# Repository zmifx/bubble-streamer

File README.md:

# How to fix S*daStream?
Somehow it happened that this bubbler stopped working-only the LEDs were flashing (no, a new power adapter did not help).
Attempts to repair the original control board did not work, it is simply too complicated for me. So I simply made a new PCB, radically simplified, built on an Arduino Micro and many of the original parts. Here are some data files. NO WARRANTY, FOR STUDY PURPOSES ONLY!
* The original one

* New PCB

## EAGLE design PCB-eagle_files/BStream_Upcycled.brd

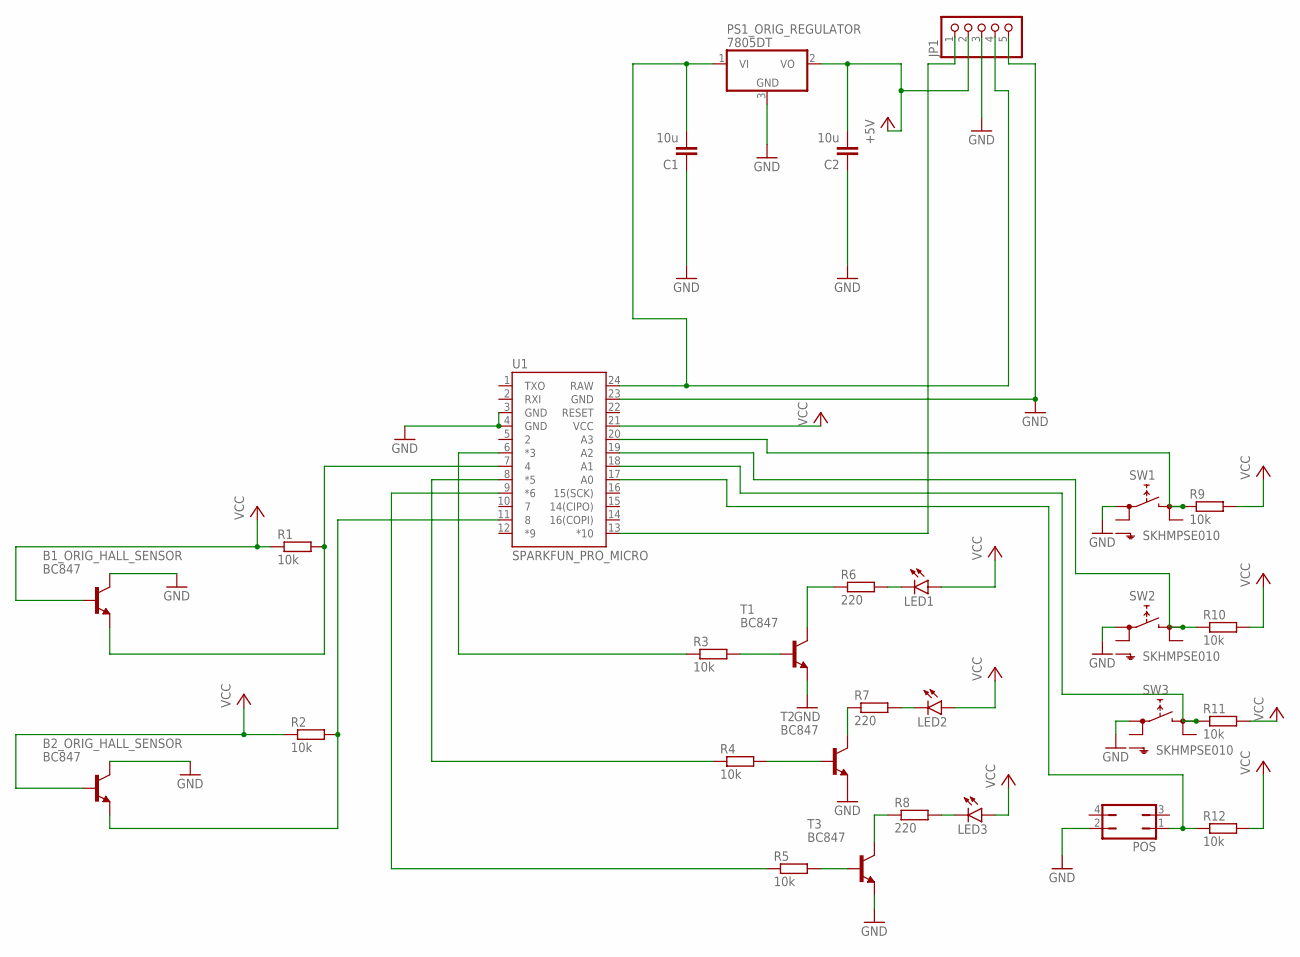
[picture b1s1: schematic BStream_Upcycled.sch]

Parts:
B1_ORIG_HALL_SENSOR, B2_ORIG_HALL_SENSOR: BC847; SOT23
C1, C2: 10u; C1206
JP1: PINHD-1X5; 1X05
LED1, LED2, LED3: LEDSML1206; SML1206
POS: JP2Q
PS1_ORIG_REGULATOR: 7805DT; TO252
R1, R2, R3, R4, R5, R9, R10, R11, R12: 10k; R1206
R6, R7, R8: 220; R1206
SW1, SW2, SW3: SKHMPSE010; SKHMPXE010
T1, T2, T3: BC847; SOT23
U1: SPARKFUN_PRO_MICRO

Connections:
+5V: C2.2, JP1.2, PS1_ORIG_REGULATOR.2 (VO)
GND: B1_ORIG_HALL_SENSOR.3 (C), B2_ORIG_HALL_SENSOR.3 (C), C1.1, C2.1, JP1.3, JP1.5, POS.2, PS1_ORIG_REGULATOR.3 (GND), SW1.1 (1.1), SW2.1 (1.1), SW3.1 (1.1), T1.2 (E), T2.2 (E), T3.2 (E), U1.3 (GND), U1.4 (GND), U1.23 (GND)
unnamed: R8.1, T3.3 (C)
unnamed: B1_ORIG_HALL_SENSOR.2 (E), R1.2, U1.7 (4)
unnamed: B2_ORIG_HALL_SENSOR.2 (E), R2.2, U1.11 (8)
unnamed: R3.1, U1.6 (*3)
unnamed: C1.2, JP1.4, PS1_ORIG_REGULATOR.1 (VI), U1.24 (RAW)
unnamed: R4.1, U1.8 (*5)
unnamed: JP1.1, U1.13 (*10)
unnamed: R5.1, U1.9 (*6)
unnamed: LED1.C, R6.2
unnamed: LED2.C, R7.2
unnamed: LED3.C, R8.2
unnamed: R6.1, T1.3 (C)
unnamed: R7.1, T2.3 (C)
unnamed: POS.1, R12.1, U1.17 (A0)
unnamed: R11.1, SW3.3 (2.1), U1.18 (A1)
unnamed: R10.1, SW2.3 (2.1), U1.19 (A2)
unnamed: R9.1, SW1.3 (2.1), U1.20 (A3)
unnamed: R5.2, T3.1 (B)
unnamed: R3.2, T1.1 (B)
unnamed: R4.2, T2.1 (B)
VCC: B1_ORIG_HALL_SENSOR.1 (B), B2_ORIG_HALL_SENSOR.1 (B), LED1.A, LED2.A, LED3.A, R1.1, R2.1, R9.2, R10.2, R11.2, R12.2, U1.21 (VCC)

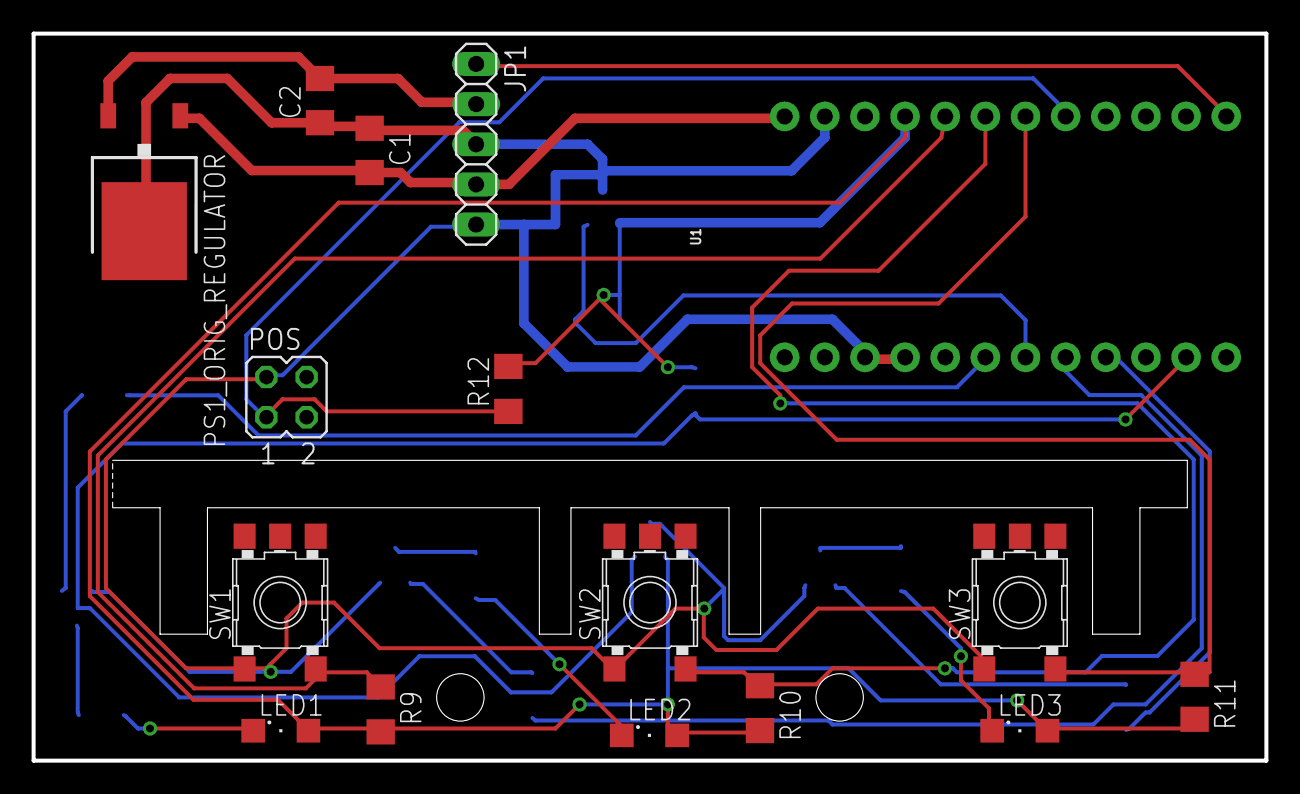
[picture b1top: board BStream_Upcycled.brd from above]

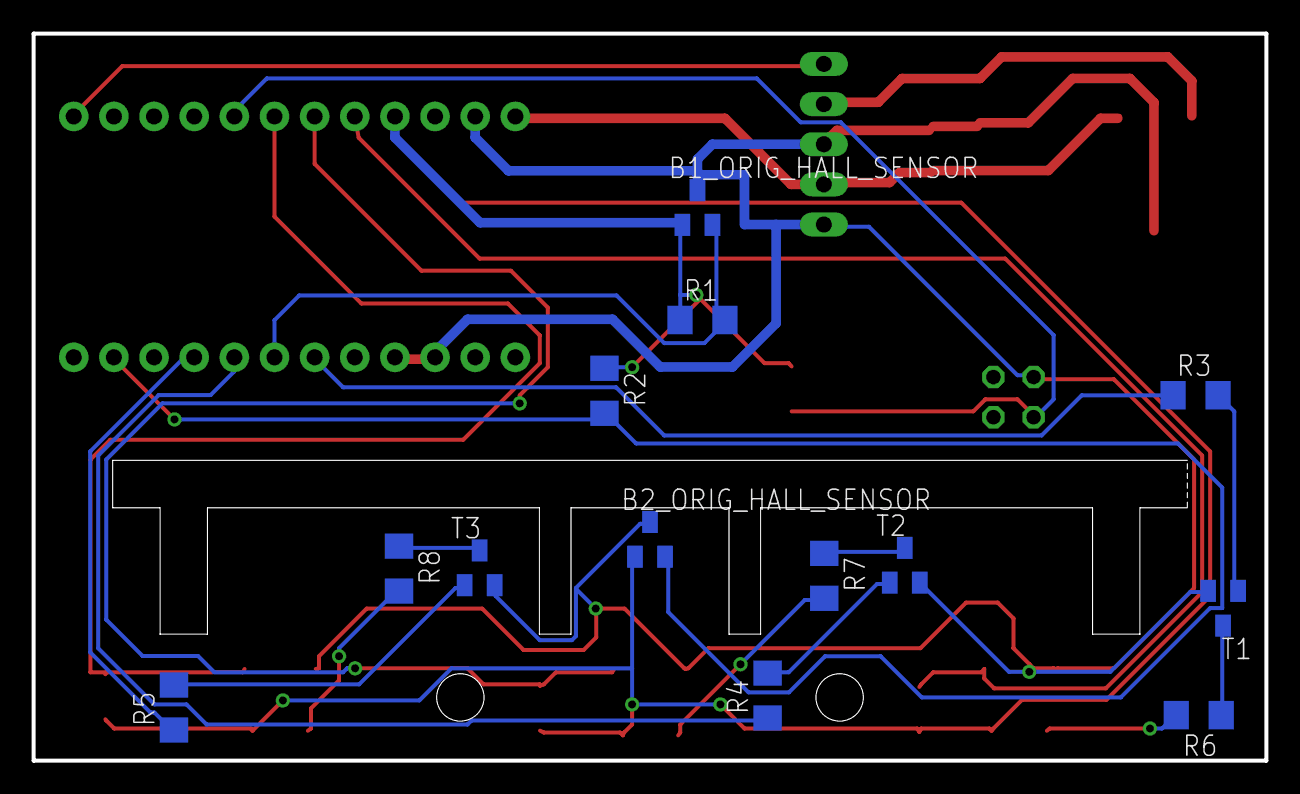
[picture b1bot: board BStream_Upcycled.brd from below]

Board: 2 copper layers, 78.0 x 46.0 mm, 29 parts (13 on the bottom side), 23 nets.

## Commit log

2024-10-26 Init servo fix

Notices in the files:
parts and their libraries:
SparkFun-Boards: Licensing: Creative Commons ShareAlike 4.0 International - https://creativecommons.org/licenses/by-sa/4.0
